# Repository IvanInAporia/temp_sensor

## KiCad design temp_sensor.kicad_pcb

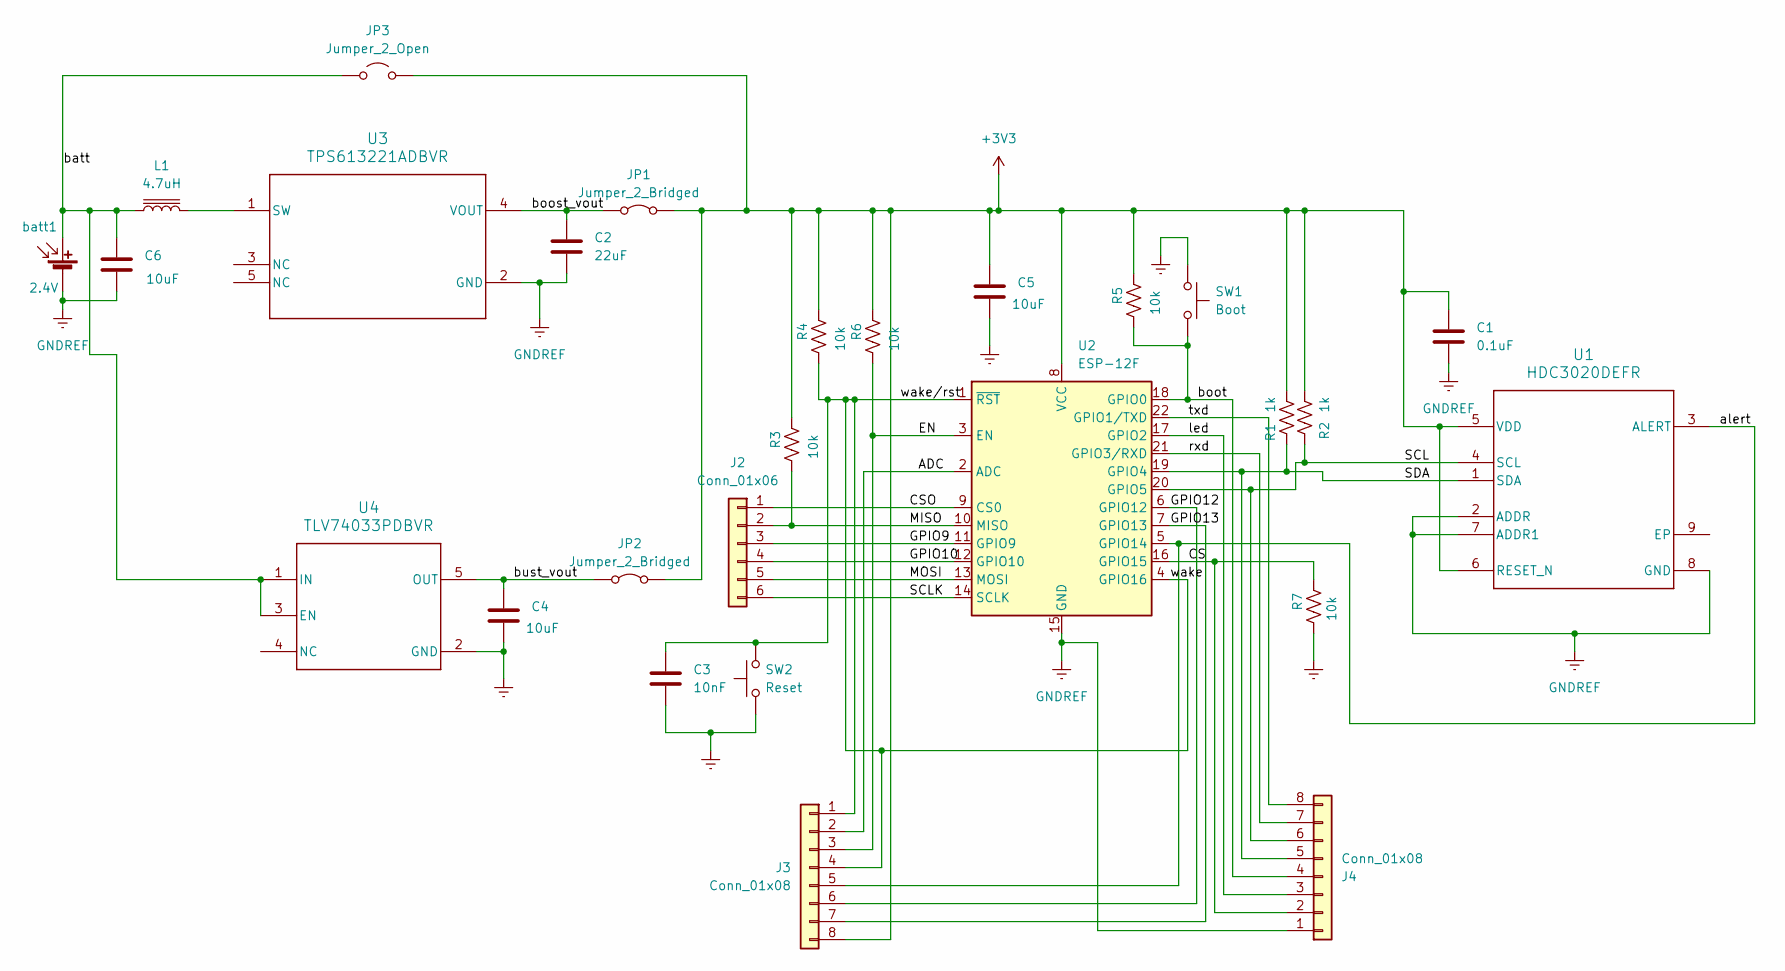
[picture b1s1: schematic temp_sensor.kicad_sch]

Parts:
C1: 0.1uF; C_0603_1608Metric_Pad1.08x0.95mm_HandSolder
C2: 22uF; C_0603_1608Metric_Pad1.08x0.95mm_HandSolder
C3: 10nF; C_0603_1608Metric_Pad1.08x0.95mm_HandSolder
C4, C5, C6: 10uF; C_0805_2012Metric_Pad1.18x1.45mm_HandSolder
J2: Conn_01x06; PinHeader_1x06_P2.54mm_Vertical
J3, J4: Conn_01x08; PinHeader_1x08_P2.54mm_Vertical
JP1, JP2: Jumper_2_Bridged; TestPoint_2Pads_Pitch2.54mm_Drill0.8mm
JP3: Jumper_2_Open; TestPoint_2Pads_Pitch2.54mm_Drill0.8mm
L1: 4.7uH; L_1210_3225Metric_Pad1.42x2.65mm_HandSolder
R1, R2: 1k; R_0805_2012Metric_Pad1.20x1.40mm_HandSolder
R3, R4, R5, R6, R7: 10k; R_0805_2012Metric_Pad1.20x1.40mm_HandSolder
SW1: Boot; SW_PUSH
SW2: Reset; SW_PUSH
U1: HDC3020DEFR; DEF0008A-IPC_A
U2: ESP-12F; ESP-12E
U3: TPS613221ADBVR; DBV0005A_M
U4: TLV74033PDBVR; DBV0005A-IPC_A
batt1: 2.4V; JST_XH_B2B-XH-A_1x02_P2.50mm_Vertical

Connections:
+3V3: C1.1, C5.1, J3.8, JP1.2 (B), JP2.2 (B), JP3.2 (B), R1.2, R2.2, R3.2, R4.2, R5.2, R6.2, U1.5 (VDD), U1.6 (RESET_N), U2.8 (VCC)
/ADC: J3.2, U2.2 (ADC)
/CS: J4.2, R7.2, U2.16 (GPIO15)
/CSO: J2.1, U2.9 (CS0)
/EN: J3.3, R6.1, U2.3 (EN)
/GPIO9: J2.3, U2.11 (GPIO9)
/GPIO10: J2.4, U2.12 (GPIO10)
/GPIO12: J3.6, U2.6 (GPIO12)
/GPIO13: J3.7, U2.7 (GPIO13)
/MISO: J2.2, R3.1, U2.10 (MISO)
/MOSI: J2.5, U2.13 (MOSI)
/SCL: J4.6, R2.1, U1.4 (SCL), U2.20 (GPIO5)
/SCLK: J2.6, U2.14 (SCLK)
/SDA: J4.5, R1.1, U1.1 (SDA), U2.19 (GPIO4)
/alert: J3.5, U1.3 (ALERT), U2.5 (GPIO14)
/batt: C6.1, JP3.1 (A), L1.1, U4.1 (IN), U4.3 (EN), batt1.1 (+)
/boost_vout: C2.1, JP1.1 (A), U3.4 (VOUT)
/boot: J4.4, R5.1, SW1.2, U2.18 (GPIO0)
/bust_vout: C4.1, JP2.1 (A), U4.5 (OUT)
/led: J4.3, U2.17 (GPIO2)
/rxd: J4.7, U2.21 (GPIO3/RXD)
/txd: J4.8, U2.22 (GPIO1/TXD)
/wake: C3.1, J3.1, J3.4, R4.1, SW2.2, U2.1 (~RST), U2.4 (GPIO16)
GNDREF: C1.2, C2.2, C3.2, C4.2, C5.2, C6.2, J4.1, R7.1, SW1.1, SW2.1, U1.2 (ADDR), U1.7 (ADDR1), U1.8 (GND), U2.15 (GND), U3.2 (GND), U4.2 (GND), batt1.2 (-)
unnamed: L1.2, U3.1 (SW)

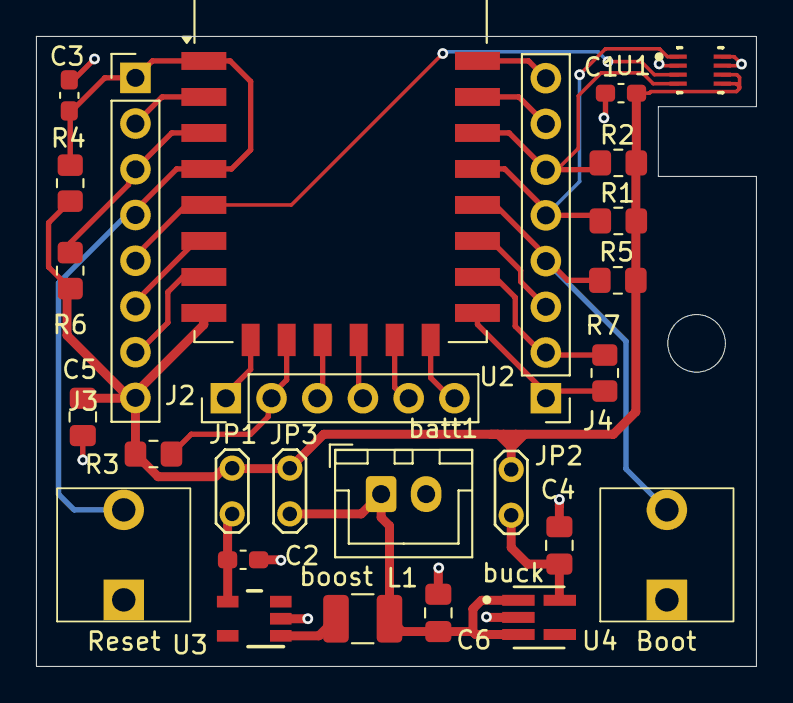
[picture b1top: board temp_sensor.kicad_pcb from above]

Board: 2 copper layers, 40.0 x 35.0 mm, 28 parts (0 on the bottom side), 25 nets.

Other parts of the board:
screw: MountingHole_3.2mm_M3_ISO7380

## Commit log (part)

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2025-05-10 Initial schematic and PCB
2025-05-11 Added cap at reset and screw hole
2025-06-09 Add ESP code on platformio
2025-06-09 Send to HA with MQTT
2025-06-09 Add ESPHome component
    It is a copy of the HDC1080 from ESPHome official repo
2025-06-09 Adapt ESPHome component for HDC302x
2025-06-09 Fix buffer name
2025-06-09 fix var declarations
2025-06-09 fix temp var
2025-06-09 Remove a couple of msgs
2025-06-09 Reduce time to read sensor
